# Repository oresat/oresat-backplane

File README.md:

# OreSat Backplane

## Background

The [OreSat](http://oresat.org) CubeSat bus uses a card cage / backplane system based on a 1 Mbps Controller Area Network (CAN) bus and a 2 cell Lithium ion battery power bus (6.0 - 8.4 V). There are ~ 8 cards per CubeSat "U", and the board is meant to be general purpose enough to allow for some card swapping. The RF lines, however, are microstrips on the backplane PCB so the backplane must be rev'd for changes in the RF cards. There are three sets of connectors:

1. 40 pin "Main" connector, which has !shutdown, CAN1, power, CAN2, OreSat power Domain (OPD) lines, and then 5 shared spare pins for custom card interconnects.
2. SMPM RF conncectors, which allows up to 3 RF connector per card and allows for 50 ohm microstrips to be run up and down the the board.
3. 20 pin "Auxiliary" connectors, used on the all but the "end" cards (top and bottom cards), which are for future inter-card communication. Good for Ethernet, for example.

The backplane now comes in two flavors: a 1U backplane, and a 2U backplane.

## Mechanical Specifications

All mechanical specifications for this board are from the SolidWorks model which is in the 'oresat-structure' repo, specifically see the 'Backplane' folder. Some notes on the mechanical design:

- Ring of bare copper on the back is for thermal contact. Assumes annodized Aluminum, so no electrical contact on this ring.
- Backplane is grounded to the Aluminum frame on the internal four fasteners; this requires preparing the Aluminum for an electrical connection.
- Square cutouts on the top and bottom are for the solar connectors to reach the end cards. Note that on the 1U backplane, the bottom cutout is not used.
- Weird cutouts above and below square solar connector cutouts are for shoulder bolts (3 mm Shoulder Diameter, 2 mm Shoulder Length, M2 x 0.4 mm Thread, McMaster Carr #[90263A111](https://www.mcmaster.com/90263a111)) that precisely locates the PCB while allowing some flexing due to differences in thermal expansion between the Aluminum frame and the PCB.
- All other fasteners are M2 x 0.4 x 4 mm.

## Electrical Specifications

The board is designed for a [4 layer stackup](https://docs.oshpark.com/services/four-layer/) from [OSH Park](https://oshpark.com/) which has better RF performance than regular 2 layer board runs.

The connectors that we use on this puppy are the:

- **1.27 mm through-hole vertical socket connectors:**
    - 40 pin main connector
       - Samtec SFM-120-01-S-D-LC
       - 3D CAD: https://www.samtec.com/partnumber/sfm-120-01-s-d-lc
       - Drawing: http://suddendocs.samtec.com/prints/sfm-1xx-xx-xxx-d-xxx-mkt.pdf
       - Brochure: http://suddendocs.samtec.com/catalog_english/sfm.pdf
       - SFM footprint: http://suddendocs.samtec.com/prints/sfm-thd.pdf
    - 20 pin auxiliary connector
       - Samtec SFM-110-01-S-D-LC
       - 3D CAD: https://www.samtec.com/partnumber/sfm-110-01-s-d-lc
       - Drawing: http://suddendocs.samtec.com/prints/sfm-1xx-xx-xxx-d-xxx-mkt.pdf
       - Brochure: http://suddendocs.samtec.com/catalog_english/sfm.pdf
       - SFM footprint: http://suddendocs.samtec.com/prints/sfm-thd.pdf

- **RF (70 cm, L band, S band)**
   - Molex 073300-011X
   - SMPM Connector Plug, Male Pin 50 Ohm Surface Mount, Through Hole Solder, $13.84/ea @ 10
   - Molex (w/CAD): https://www.molex.com/molex/products/datasheet.jsp?part=active/0733000110_RF_COAX_CONNECTORS.xml&channel=Products&Lang=en-US
   - We've done a detailed characteraziation of OSH Park's 4 layer process, and found that 0.38 mm is the correct width for a 50 ohm microstrip.

- **CAN termination**
   - We'll use split termination, using two 60 ohm resistors with a center tapped capacitor for reduced EMI.
   - Resistors
      - 60.4 +/- 1% ohms. Might consider higher if the number of notes (~ 20) adds too much parallel resistance)
      - Usually there's only 2V (differential) across the 120 ohm termination resistors = 16 mA = 33 mW of power dissipation.
      - In the event of a bus short, there's 8.4 V across 120 ohms is 70 mA = 590 mW of power dissipation. That's ~ 300 mW across each of the 60 ohm resistors. Yikes.
      - ISO 11898-2 also requires 220 mW for the termination resistors, for whatever that's worth.
      - There exist 0.5 W 1206 resistors (?!) so although that's for an air rating, we'll still choose it, since larger than 1206 resistors are a tight fit
   - Capacitor
      - ISO 11898-2 doesn't seem to say anything about the capacitance, and the internets tend to say weird things. Unclear on this value.
      - TI's [Controller Area Network Physical Layer Requirements](http://www.ti.com/lit/an/slla270/slla270.pdf) suggests 4.7 nF to make the f_3dB = 1.1 MHz.
      - Seems awfully close to our 1 Mbps bus, so let's bump that down to 1 nF which is f_3db = 5.3 MHz.

- **Debug connector**
   - Harwin M55-6001642R (same family as the solar and end cap connectors)
   - Located on the back side of the backplane, it's a 16 pin 1.27 mm connector that gives external access to CAN busses, VBUS, and the UART lines. It sits in the 1U solar module "cutout".
   - For the external connector board, see the `backplane-debug` folder in the `oresat-flatsat` repo.

## Versions

- 1U
   - v1.0 - First fabbed 1U, but never assembled. For old frames (v1.1 frames), no -Z end cap connector, no debug connector.
   - v1.1 - Added -Z end cap connector. Fabbed roughly 2020-09-01, two assembled.
   - v1.2 - Added 1.27 mm debug connector, which tended to short. Fabbed 2020-12-08. Originally delivered on OreSat0.0 but never flown.
   - v2.0 -new backplane "v2" signal pinout (less power, more signals, UART lines, CAN bus bridging) and new non-shorting debug connector. Made new debug port board and breakout. Also corrected RF ports, including L1 band microstrip and S band strip to -Z end cap. Fabbed 2021-11-01 and installed on OreSat0.1 handed off to Spaceflight, ready for launch!
- 2U
   - v1.0 - First backplane. 2 layer board, RF connector array, aux and main connectors. Fabbed 2018/10/02.
   - v1.1 - End Cards now use 40 pin connector, solar connectors now actually fit. Fabbed 2019/02/25.
   - V2.0 - Switched to 4 layer board, removed RF connector array, used actual microstrips tuned to the 4 layer OSH Park process. Fabbed 2019/07/01.
   - v2.1 - Updated to latest backplane DXF, reducing all sides by 0.15 mm. Fixed solar connector cutout areas that were lopsided. Added CAN termination resistors. Moved RF connectors to latest (2020/02/15) locations. NOT YET FABBED.
   - vHASP - Made for the NASA HASP mission, fabbed, but never used.
   - V2.2 - Updated to FrameV2 and Oresat0.5 card locations

## LICENSE

Copyright the Portland State Aerospace Society, 2022.

This source describes Open Hardware that is licensed under CERN-OHL-S v2, or any later version.

You may redistribute and modify this source and make products using it under the terms of the CERN-OHL-S v2 (https://ohwr.org/cern_ohl_s_v2.txt).

This source is distributed WITHOUT ANY EXPRESS OR IMPLIED WARRANTY, INCLUDING OF MERCHANTABILITY, SATISFACTORY QUALITY AND FITNESS FOR A PARTICULAR PURPOSE. Please see the CERN-OHL-S v2 for applicable conditions.

Source location: https://github.com/oresat/

As per CERN-OHL-S v2 section 4, should You produce hardware based on this source, You must where practicable maintain the Source Location visible on the external case of the Gizmo or other products you make using this source.

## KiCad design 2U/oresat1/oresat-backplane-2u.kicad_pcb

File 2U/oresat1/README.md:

---
title: "**OreSat1 2U Backplane Fabrication and Assembly Information**"
subtitle: |
  **Fabrication and Assembly Information**\
  For build TIME-STAMP
fontsize: 10pt
geometry:
  - margin=0.5in
toc: true
toc-depth: 2
colorlinks: true
urlcolor: blue
---

\newpage

# About this Board

## Board Description

The OreSat1 2U Backplane is the backplane for a 2U CubeSat based on the open source [OreSat CubeSat system](https://www.oresat.org/). The backplane has:

- 40 pin main connnectors for Oresat-based cards
- Bus voltage (2S Lithium Ion batteries with a Vnom of 7.2V)
- Two CAN busses for inter-card communication
- RF lines using SMPM RF connectors and microstrips
- A debug connector to carry critical lines to the outside of the CubeSat
- Two cutouts for solar module connections

## Documentation Links

- OreSat Backplane hardware Git repository: <https://github.com/oresat/oresat-backplane>
- **TODO:** Backplane Design Notes + Design Review Notes

## Documentation Files

| Filename                        | Notes                                    |
| ------------------------------- | ---------------------------------------- |
| README.pdf                      | This README file                         |
| PROJECT-NAME-outline.dxf        | Board outline (with holes) in DXF format |
| PROJECT-NAME-pcba.step          | 3D model of PCBA (with components)       |
| PROJECT-NAME-render-bot.jpg     | Render of the top of the 3D model        |
| PROJECT-NAME-render-bot.jpg     | Render of the bottom of the 3D model     |
| PROJECT-NAME-schematic.pdf      | PDF of board schematics                  |

## Contact Information

- Website: <https://www.oresat.org/>
- Email: <oresat@pdx.edu>
- Instagram: @pdxaerospace

## Board Renders

{width=50%}
{width=50%}

\newpage

# Printed Circuit Board (PCB) Fabrication Information

## Board Info

- 4 layer board
- Bounding box is 82.5 x 213.5 mm
- Board thickness is 1.59 mm (0.063 inch)
- **Important:** See Materials and Stack Up sections below

## Board Requirements

- Design Rules
    - Minimum Trace / Space design rules
       - Outer layers: 0.127 mm (5.0 mil) / 0.127 mm (5.0 mil)
       - Inner layers: 0.127 mm (5.0 mil) / 0.127 mm (5.0 mil)
    - Outer dimension router tolerance: +/- 0.254 mm (10.0 mil)
    - Hole placement tolerance: +/- 0.075 mm (3.0 mil)
    - Inner tab routed slot tolerance: +/- 0.254 mm (10.0 mil)
- Drills
   - Drill Positional Tolerance: 0.051 mm (2.0 mil)
   - Drill Size tolerance: +/- 0.064 mm (2.5 mil)
- Plated/Un-plated holes
  - PTH minimum diameter: 0.254 mm (10 mil)
  - PTH minimum annulus: 0.102 mm (4 mil) radius
  - There are 4 un-plated (NPT) holes
- Outline/Routing
  - Requires a 1.0 mm or smaller diameter routing bit
- Slots/Cutouts
  - There are two slot/cutouts.
  - Requires a 1.0 mm or smaller diameter routing bit
- There are 3 fiducials on the top layer and 3 fiducials on the bottom layer.
- Panel tabs ("mouse bites")
   - Card edges must be smooth; no mouse bites or other intrusions into the card outline.
   - If external mouse bites are required, minimize and customer will remove by hand before assembly.
- If not otherwise specified, PCB fabrication shall conform to IPC-6012, Class 2 or better. 
- If not otherwise specified, PCB acceptability criteria shall be via IPC-A-600, Class 2 or better.

## Materials

- Controlled impedance
   - The stackup is critical for the performance of high speed signals on this board.
   - As long as the stackup is controlled, the board is not considered controlled impedance.
- Isola FR408HR or material with equivalent Dk.
- Board Surface treatment should be ENIG, althogh immersion Silver is acceptable.
- White silkscreen on top and bottom surface
- Taiyo PSR-4000 or equivalent soldermask on top and bottom, no requirements for color.

## Stack Up

| Layer         | Thickness           | Notes                                        |
|---------------|---------------------|----------------------------------------------|
| Top Copper    | 0.043 mm /  1.7 mil |  Layer 1 foil, 1 oz Cu after plating         |
| prepreg       | 0.200 mm /  7.9 mil |  Prepreg - Isola FR408HR 2113                |
| Layer 2       | 0.018 mm /  0.7 mil |  Layer 2 foil, 0.5 oz Cu                     |
| Core          | 0.991 mm /   39 mil |  Core Isola FR408HR                          |
| Layer 3       | 0.018 mm /  0.7 mil |  Layer 3 foil, 0.5 oz Cu                     |
| prepreg       | 0.200 mm /  7.9 mil |  Prepreg - Isola FR408HR 2113                |
| Bottom Copper | 0.043 mm /  1.7 mil |  Layer 4 foil, 1 oz copper after plating     |
| **Total Stackup** | **1.588 mm / 62.5 mil** |                                      |

## Array / Panel Information

- Coordinate with Contract Manufacturer (CM) for optimal size of this panel.
- If no feedback from CM, then produce single boards (no panel).

## Fabrication Files

### IPC-2581 File

| Filename                 | Notes                                   |
| ------------------------ | --------------------------------------- |
| PROJECT-NAME-ipc2581.xml | IPC-2581 board information file         |

### Legacy PCB Files

| Filename                      | Notes                                         |
| ------------------------------| --------------------------------------------- |
| PROJECT-NAME-Edge_Cuts.gbr    | RS274X file for the dimension (outline) layer |
| PROJECT-NAME-F_Silkscreen.gbr | RS274X file for the top silkscreen            |
| PROJECT-NAME-F_Mask.gbr       | RS274X file for the top soldermask            |
| PROJECT-NAME-F_Cu.gbr         | RS274X file for the top copper layer          |
| PROJECT-NAME-In1_Cu.gbr       | RS274X file for the layer 2 copper            |
| PROJECT-NAME-In2_Cu.gbr       | RS274X file for the layer 3 copper            |
| PROJECT-NAME-B_Cu.gbr         | RS274X file for the bottom copper layer       |
| PROJECT-NAME-B_Mask.gbr       | RS274X file for the bottom soldermask         |
| PROJECT-NAME-B_Silkscreen.gbr | RS274X file for the bottom silkscreen         |
| PROJECT-NAME-NPTH.drl         | Excellon file for non-plated through holes    |
| PROJECT-NAME-PTH.drl          | Excellon file for plated through holes        | 

\newpage

# Printed Circuit Board Assembly (PCBA) Information

## Assembly Info

- There are components on the top and bottom sides of the board.
- This PCBA is a mix of surface mount (SMT) and through hole (THT) components.

## Assembly Requirements

- Assembly shall conform to IPC J-STD-001 Class 2 or better.
- Inspection of assemblies shall be per IPC-A-610, Class 2 or better.
- Bake components that are not moisture sealed to appropriate levels as required.
- Solder paste MUST be leaded.
- Aqueous flux and wash strongly preferred.
   - Clean to NASA Standard "Visibly Clean (VC)": No particles or residues are visible to the naked eye.
- No conformal coating.
- Ship in antistatic protective bag.

## Component Specific Assembly Information

- SMPM connectors (CM*.*) should be hand-added before reflow.

## Assembly Files

### IPC-2581 File

| Filename                 | Notes                           |
| ------------------------ | ------------------------------- |
| PROJECT-NAME-ipc2581.xml | IPC-2581 board information file |

### Bill of Materials (BOM)

| Filename             | Description                            |
| -------------------- | -------------------------------------- |
| PROJECT-NAME-bom.csv | BOM in Comma Separated Variable format |

### Solder Paste Stencils

| Filename                 | Notes                                            |
| ------------------------ | ------------------------------------------------ |
| PROJECT-NAME-B_Paste.gbr | RS274X file for top/front solder paste stencil   |
| PROJECT-NAME-F_Paste.gbr | RS274X file for bottom/back solder paste stencil |

### Mounting/Placement Location

| Filename            | Description                                 |
| ------------------- | ------------------------------------------- |
| PROJECT-NAME-3u.pos | Pick and place locations for components     |

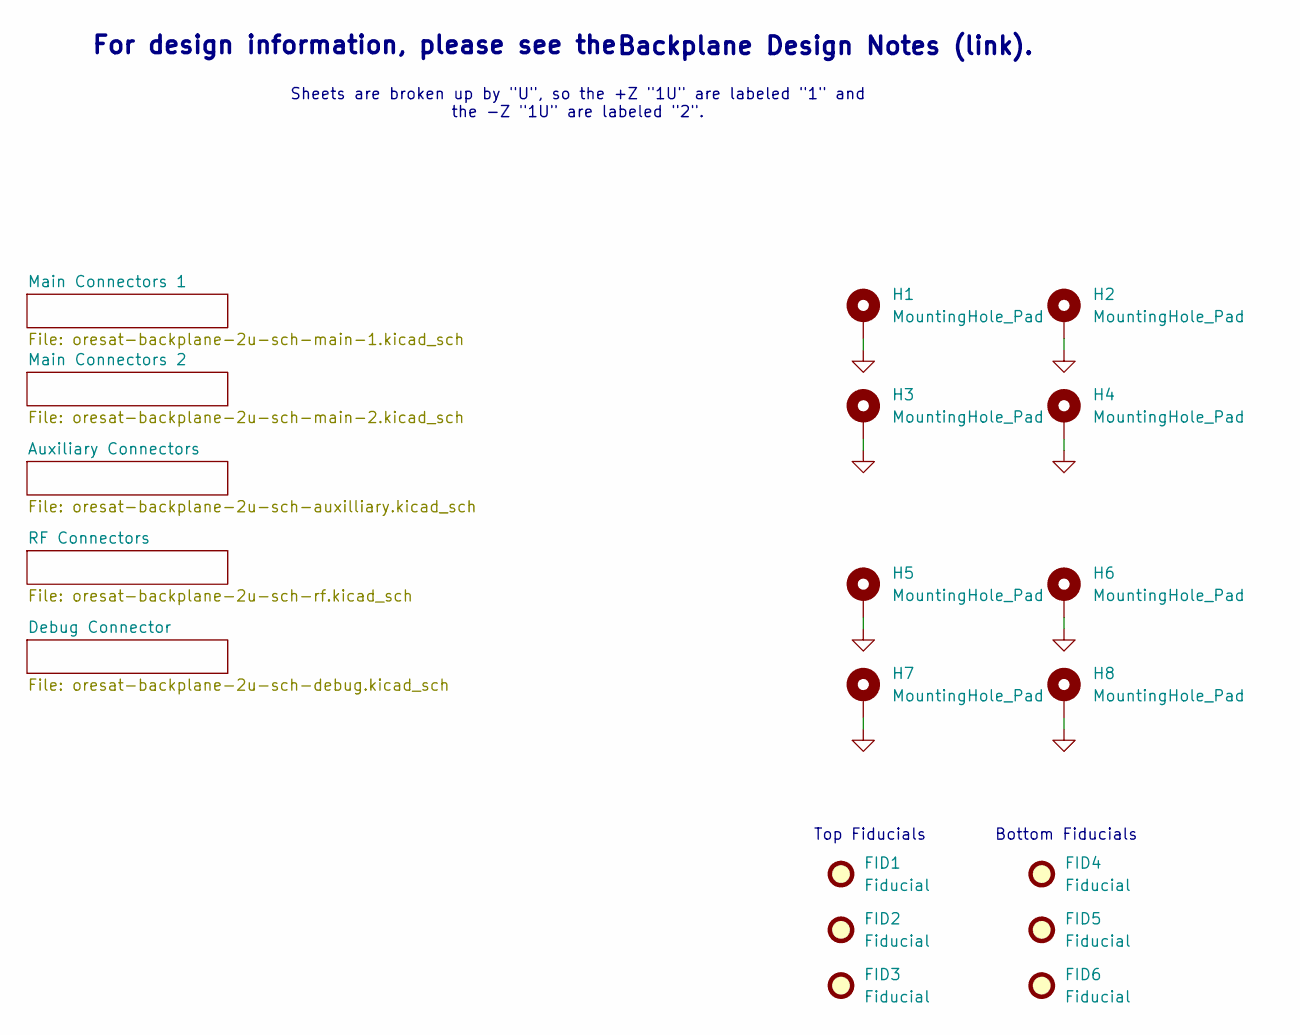
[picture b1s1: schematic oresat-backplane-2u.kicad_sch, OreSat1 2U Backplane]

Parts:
FID1, FID2, FID3, FID4, FID5, FID6: Fiducial; Fiducial_1mm_Mask2mm
H1, H2, H3, H4, H5, H6, H7, H8: MountingHole_Pad; MountingHole_2.2mm_M2_DIN965_Pad

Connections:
GND: H1.1 (1_1), H2.1 (1_1), H3.1 (1_1), H4.1 (1_1), H5.1 (1_1), H6.1 (1_1), H7.1 (1_1), H8.1 (1_1); also elsewhere on the board

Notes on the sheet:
For design information, please see the
Top Fiducials
Sheets are broken up by "U", so the +Z "1U" are labeled "1" and the -Z "1U" are labeled "2".
Backplane Design Notes (link).
Bottom Fiducials

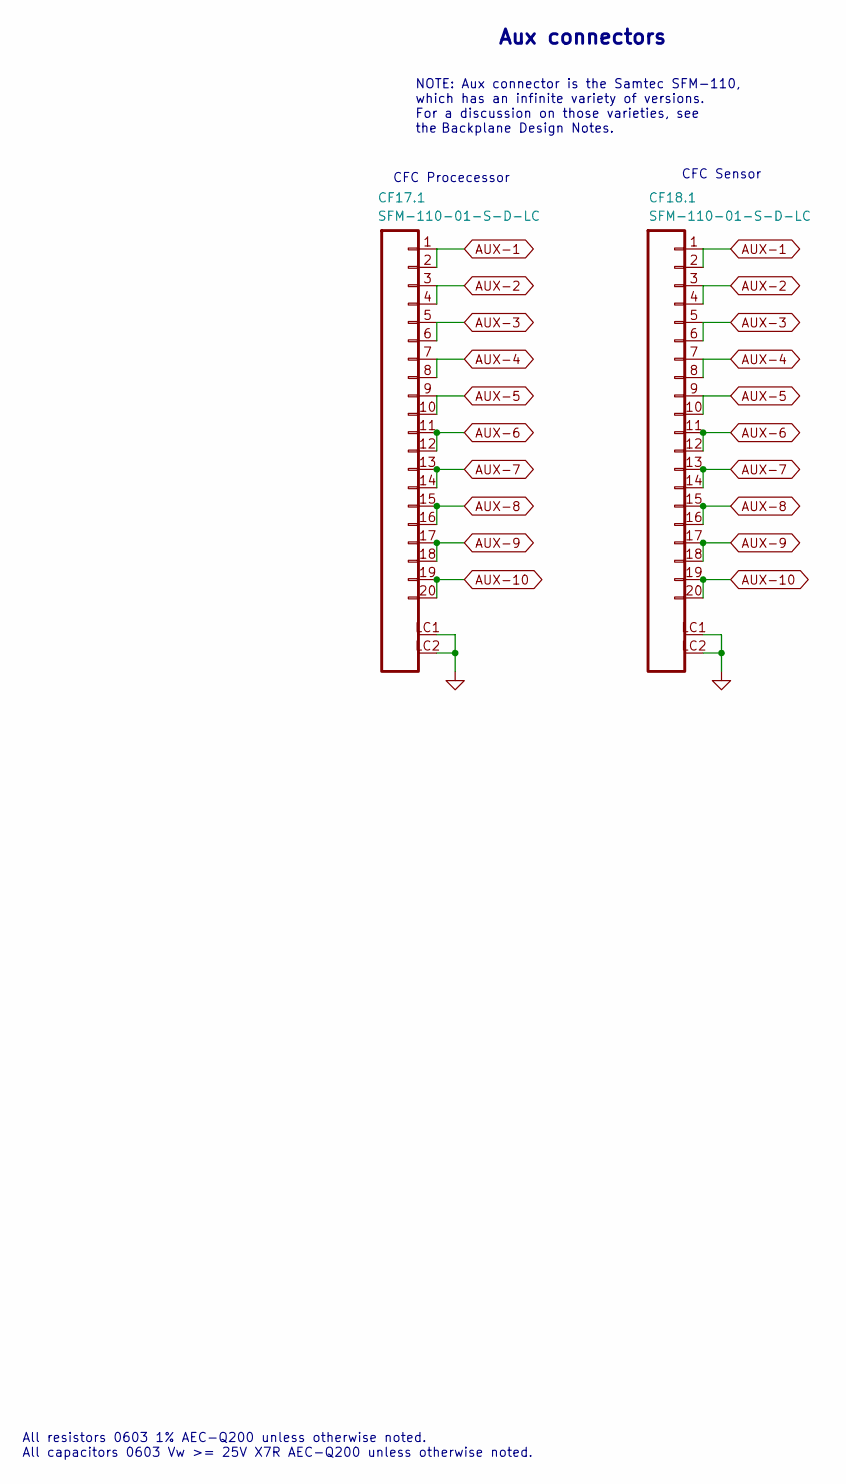
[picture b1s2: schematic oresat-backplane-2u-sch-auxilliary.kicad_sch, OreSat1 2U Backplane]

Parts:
CF17.1, CF18.1: SFM-110-01-S-D-LC; J-SAMTEC-CF-SFM-110-X1-XXX-D-LC; MPN SFM-110-01-S-D-LC

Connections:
AUX-1: CF17.1.1, CF17.1.2, CF18.1.1, CF18.1.2
AUX-2: CF17.1.3, CF17.1.4, CF18.1.3, CF18.1.4
AUX-3: CF17.1.5, CF17.1.6, CF18.1.5, CF18.1.6
AUX-4: CF17.1.7, CF17.1.8, CF18.1.7, CF18.1.8
AUX-5: CF17.1.9, CF17.1.10, CF18.1.9, CF18.1.10
AUX-6: CF17.1.11, CF17.1.12, CF18.1.11, CF18.1.12
AUX-7: CF17.1.13, CF17.1.14, CF18.1.13, CF18.1.14
AUX-8: CF17.1.15, CF17.1.16, CF18.1.15, CF18.1.16
AUX-9: CF17.1.17, CF17.1.18, CF18.1.17, CF18.1.18
AUX-10: CF17.1.19, CF17.1.20, CF18.1.19, CF18.1.20
GND: CF17.1.LC1, CF17.1.LC2, CF18.1.LC1, CF18.1.LC2; also elsewhere on the board

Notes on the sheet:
Backplane Design Notes.
CFC Procecessor
All resistors 0603 1% AEC-Q200 unless otherwise noted. All capacitors 0603 Vw >= 25V X7R AEC-Q200 unless otherwise noted.
CFC Sensor
NOTE: Aux connector is the Samtec SFM-110, which has an infinite variety of versions. For a discussion on those varieties, see the
Aux connectors

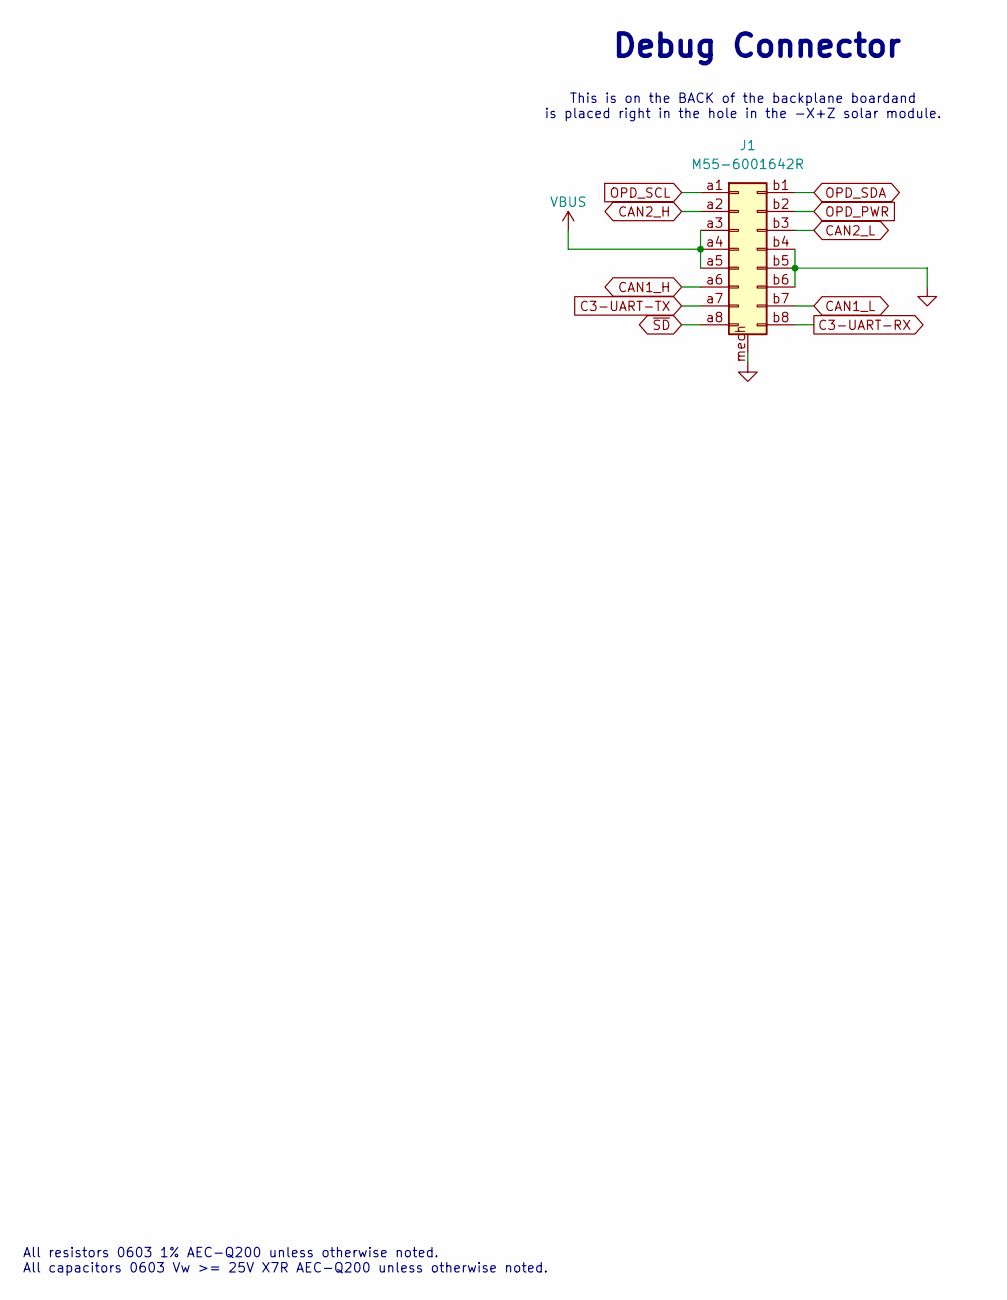
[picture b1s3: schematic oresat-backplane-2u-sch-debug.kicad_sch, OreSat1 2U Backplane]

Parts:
J1: M55-6001642R; m55-6001642; MPN M55-6001642R

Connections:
C3-UART-RX: J1.b8; also elsewhere on the board
C3-UART-TX: J1.a7; also elsewhere on the board
CAN1_H: J1.a6; also elsewhere on the board
CAN1_L: J1.b7; also elsewhere on the board
CAN2_H: J1.a2; also elsewhere on the board
CAN2_L: J1.b3; also elsewhere on the board
GND: J1.b4, J1.b5, J1.b6, J1.mech; also elsewhere on the board
OPD_PWR: J1.b2; also elsewhere on the board
OPD_SCL: J1.a1; also elsewhere on the board
OPD_SDA: J1.b1; also elsewhere on the board
VBUS: J1.a3, J1.a4, J1.a5; also elsewhere on the board
~SD: J1.a8; also elsewhere on the board

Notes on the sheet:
This is on the BACK of the backplane boardand is placed right in the hole in the -X+Z solar module.
Debug Connector
All resistors 0603 1% AEC-Q200 unless otherwise noted. All capacitors 0603 Vw >= 25V X7R AEC-Q200 unless otherwise noted.

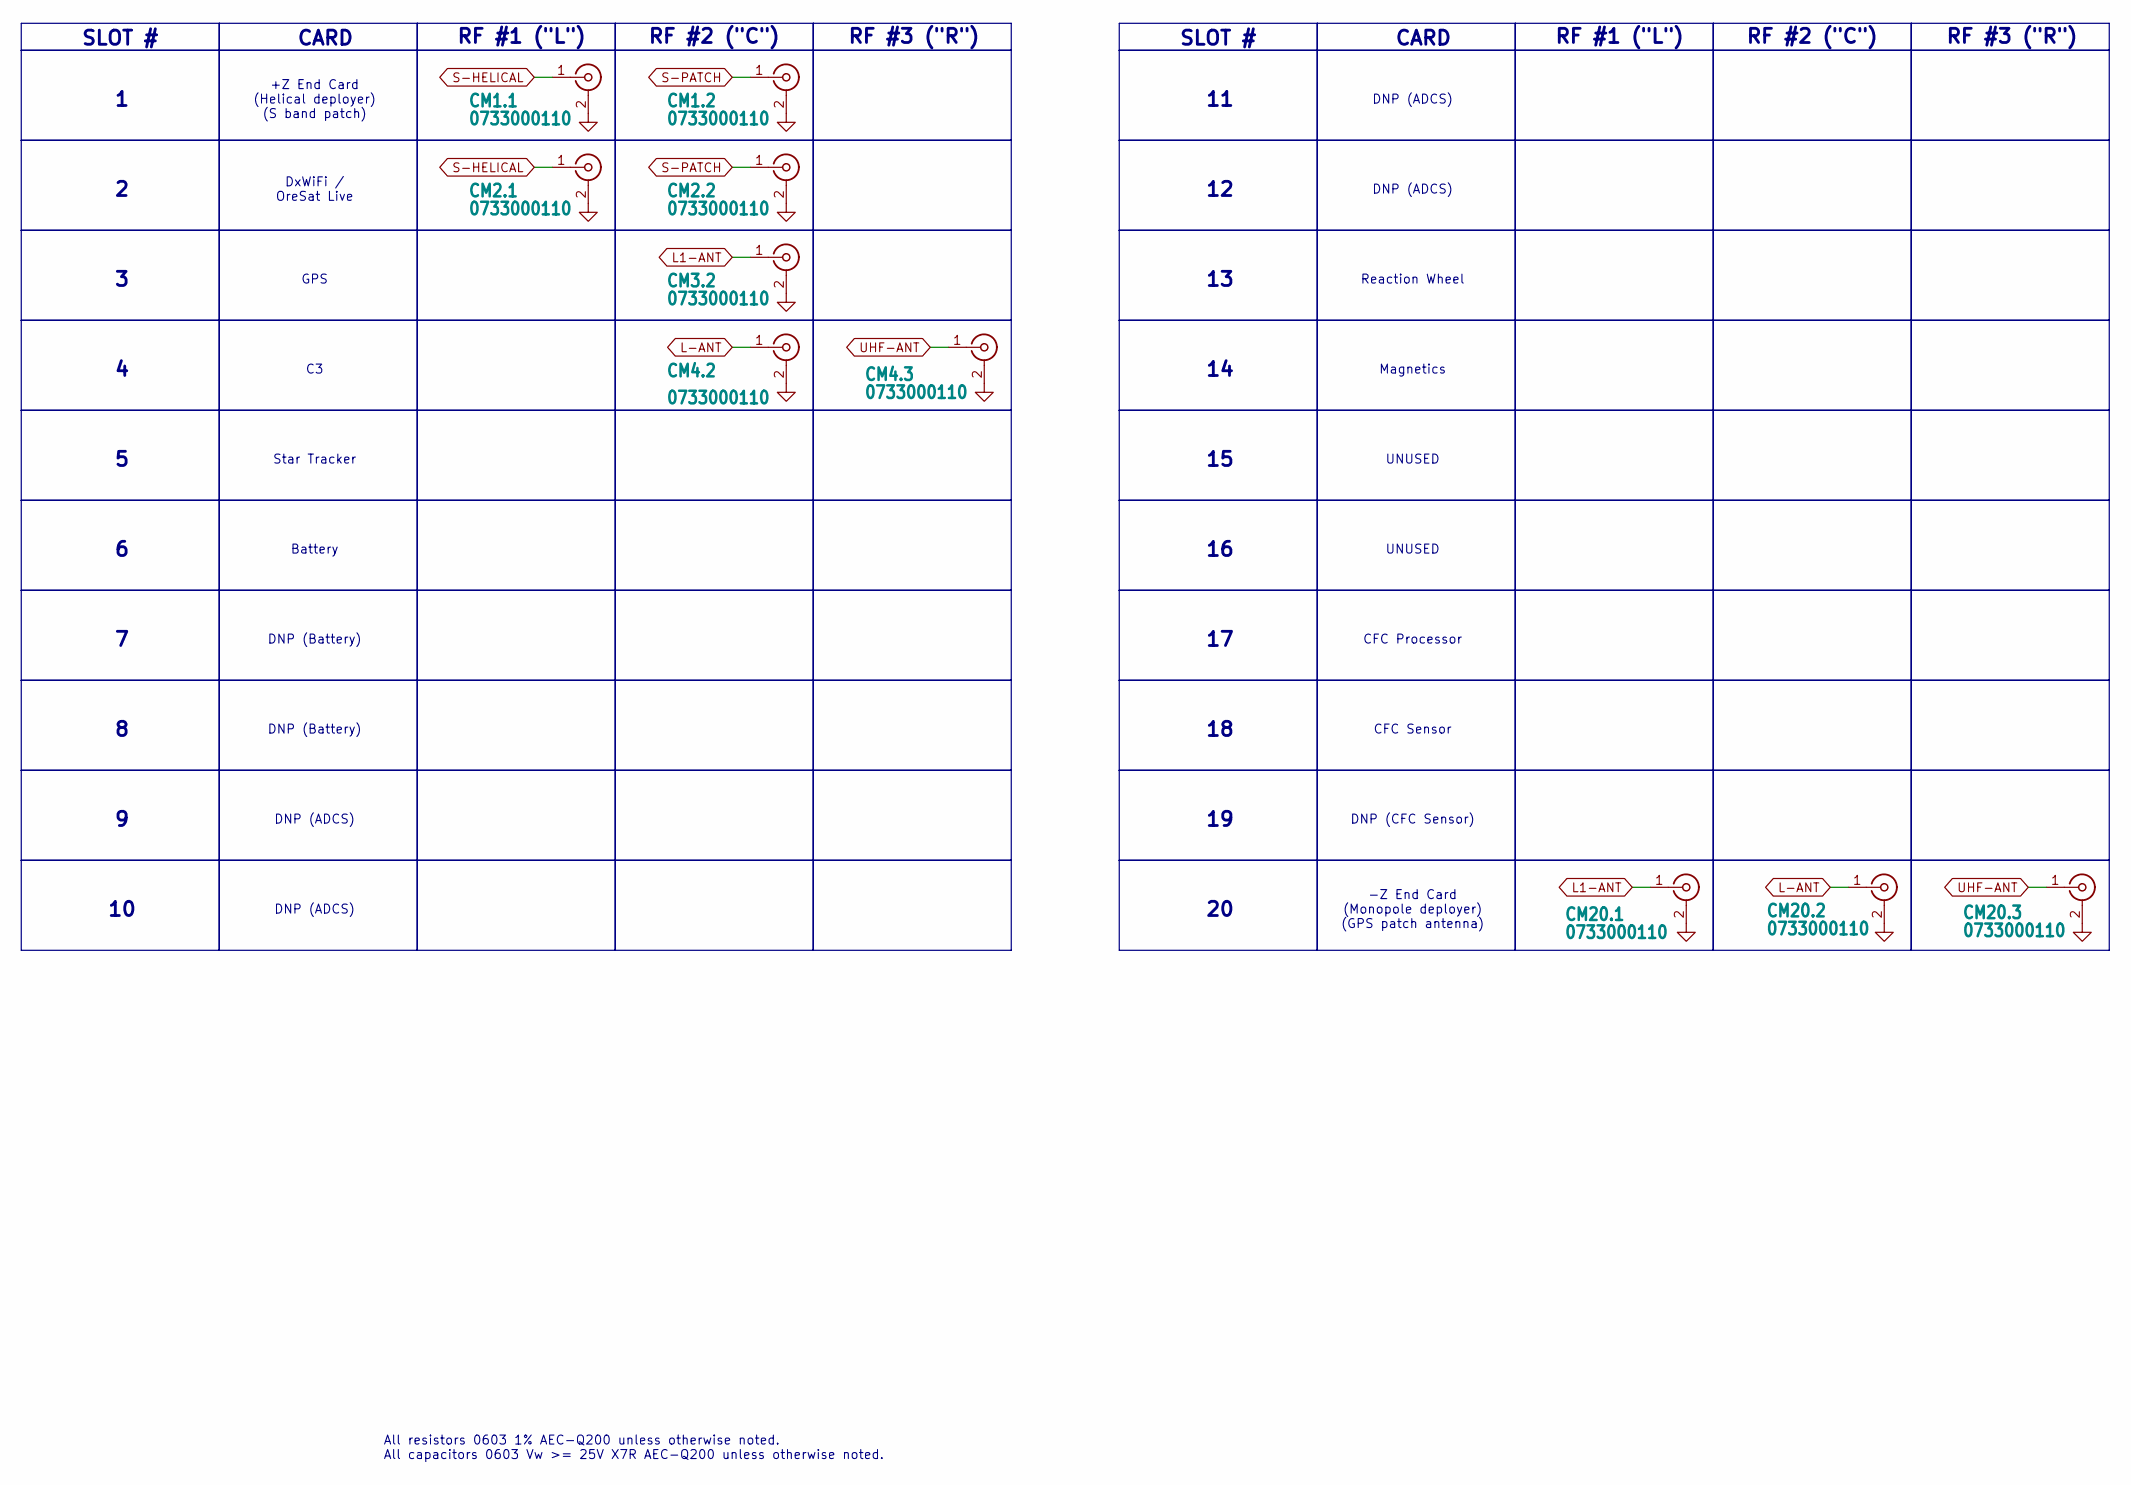
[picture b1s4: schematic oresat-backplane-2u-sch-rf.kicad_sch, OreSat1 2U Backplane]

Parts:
CM1.1, CM1.2, CM2.1, CM2.2, CM3.2, CM4.2, CM4.3, CM20.1, CM20.2, CM20.3: 0733000110; J-MOLEX-SMPM-73300-011X; MPN 0733000110

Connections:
GND: CM1.1.2 (Ext), CM1.2.2 (Ext), CM2.1.2 (Ext), CM2.2.2 (Ext), CM3.2.2 (Ext), CM4.2.2 (Ext), CM4.3.2 (Ext), CM20.1.2 (Ext), CM20.2.2 (Ext), CM20.3.2 (Ext); also elsewhere on the board
L1-ANT: CM3.2.1 (In), CM20.1.1 (In)
L-ANT: CM4.2.1 (In), CM20.2.1 (In)
S-HELICAL: CM1.1.1 (In), CM2.1.1 (In)
S-PATCH: CM1.2.1 (In), CM2.2.1 (In)
UHF-ANT: CM4.3.1 (In), CM20.3.1 (In)

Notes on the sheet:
CARD
SLOT #
+Z End Card (Helical deployer) (S band patch)
RF #2 ("C")
RF #3 ("R")
DxWiFi / OreSat Live
UNUSED
Star Tracker
Battery
DNP (CFC Sensor)
GPS
RF #1 ("L")
DNP (ADCS)
CFC Sensor
Magnetics
CFC Processor
-Z End Card (Monopole deployer) (GPS patch antenna)
DNP (Battery)
Reaction Wheel
All resistors 0603 1% AEC-Q200 unless otherwise noted. All capacitors 0603 Vw >= 25V X7R AEC-Q200 unless otherwise noted.

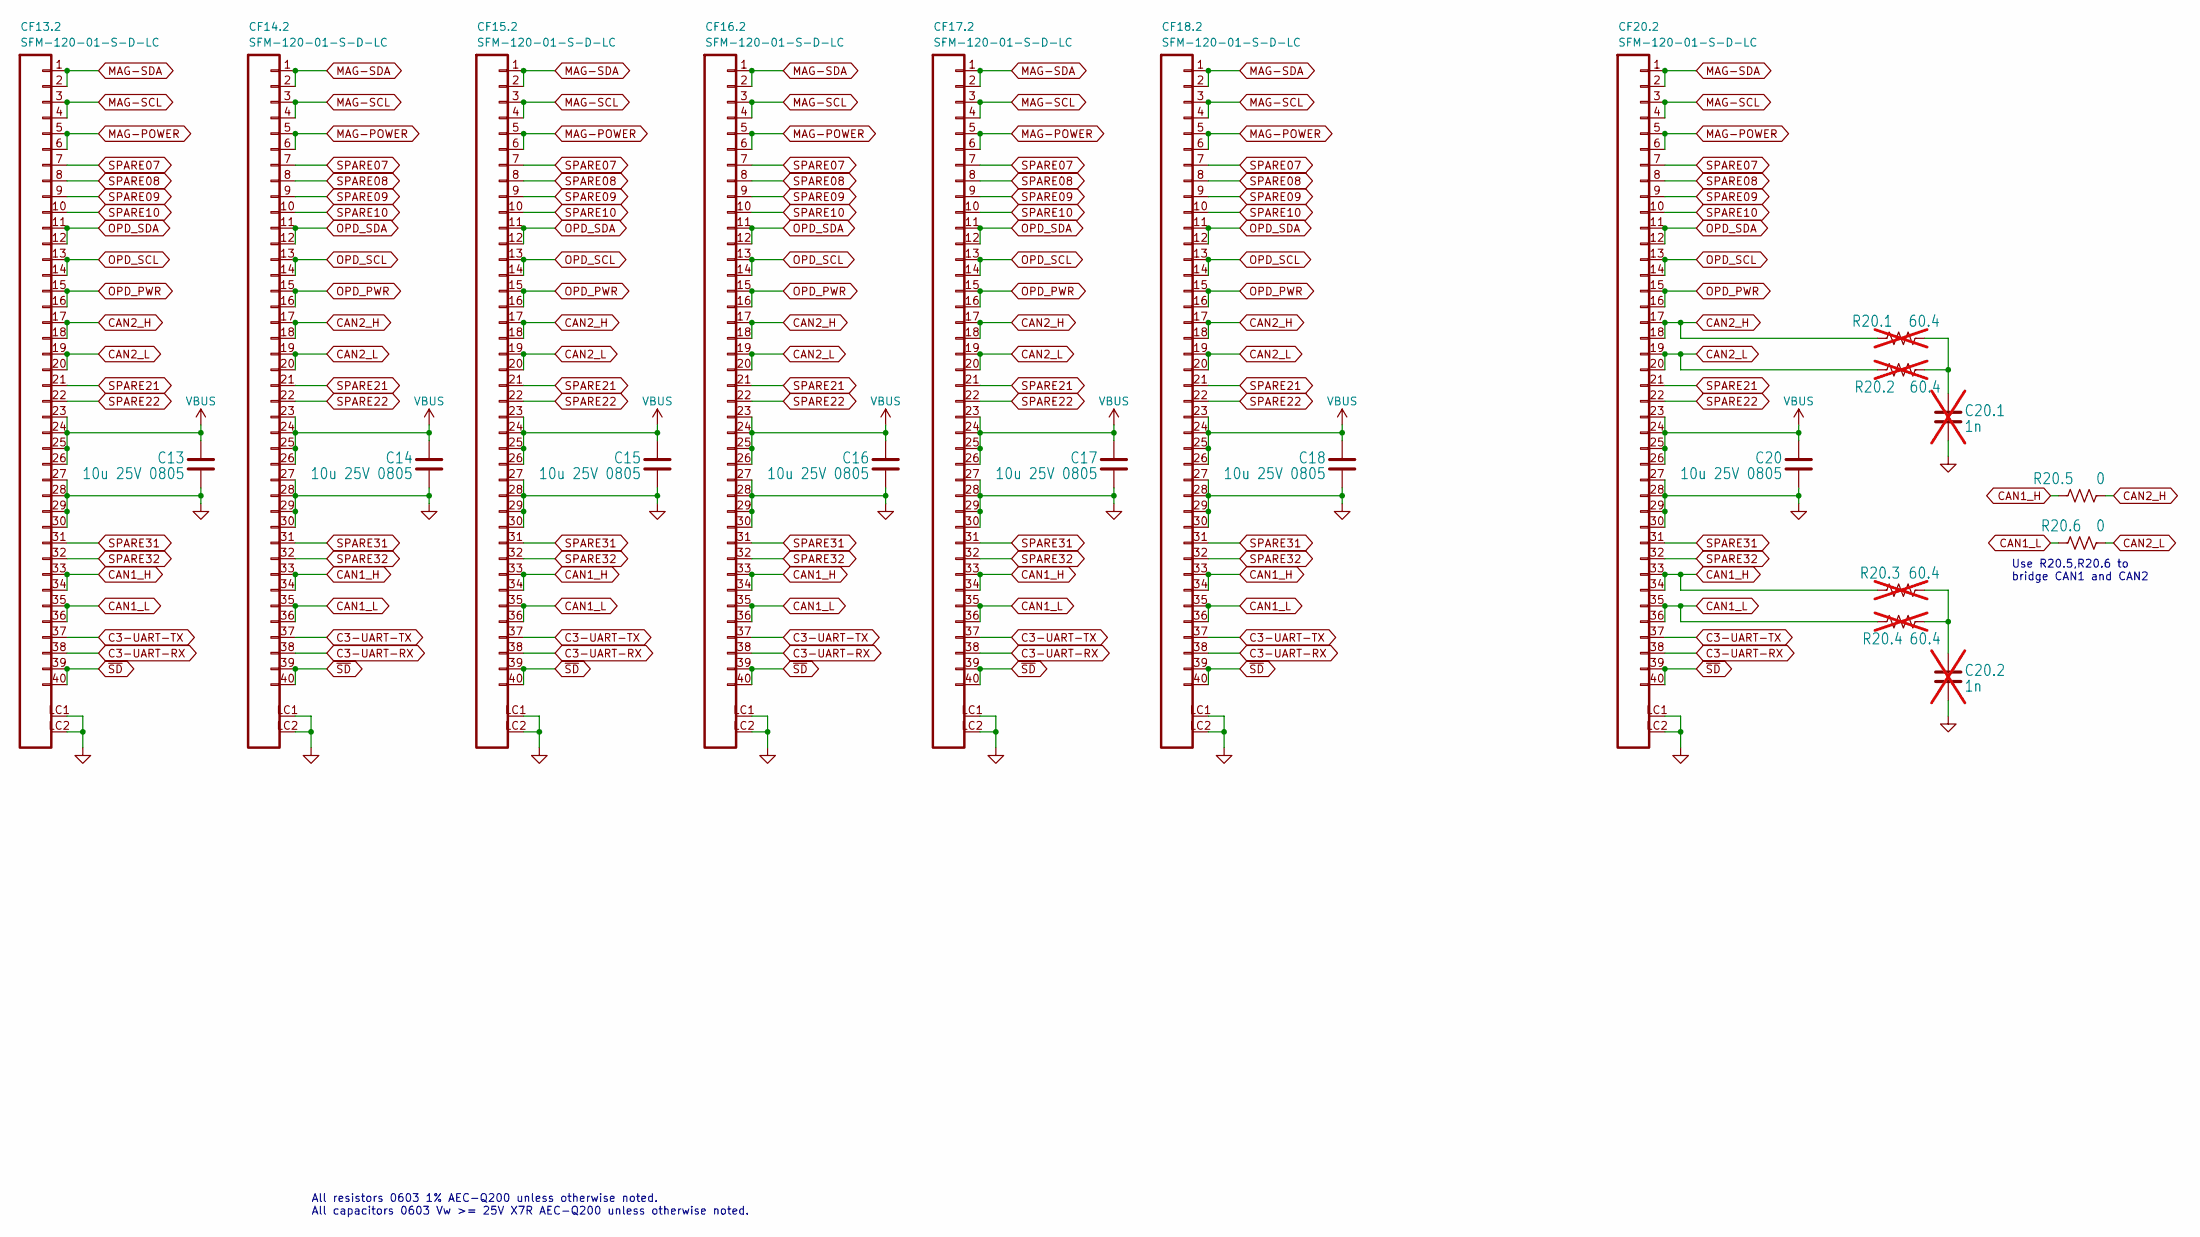
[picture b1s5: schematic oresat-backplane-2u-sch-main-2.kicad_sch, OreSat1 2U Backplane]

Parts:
C13, C14, C15, C16, C17, C18, C20: 10u 25V 0805; C_1206_3216Metric; MPN GRT31CR71E106KE13L
C20.1, C20.2: 1n; 0603-C-NOSILK; MPN C0603C102J5GECAUTO; not fitted
CF13.2, CF14.2, CF15.2, CF16.2, CF17.2, CF18.2, CF20.2: SFM-120-01-S-D-LC; J-SAMTEC-SFM-120-X1-XXX-D; MPN SFM-120-01-S-D-LC
R20.1, R20.2, R20.3, R20.4: 60.4; R_1206_3216Metric; MPN RMCF1206FT60R4; not fitted
R20.5, R20.6: 0; 0603-C-NOSILK; MPN RMCF0603ZT0R00

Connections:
C3-UART-RX: CF13.2.38, CF14.2.38, CF15.2.38, CF16.2.38, CF17.2.38, CF18.2.38, CF20.2.38; also elsewhere on the board
C3-UART-TX: CF13.2.37, CF14.2.37, CF15.2.37, CF16.2.37, CF17.2.37, CF18.2.37, CF20.2.37; also elsewhere on the board
CAN1_H: CF13.2.33, CF13.2.34, CF14.2.33, CF14.2.34, CF15.2.33, CF15.2.34, CF16.2.33, CF16.2.34, CF17.2.33, CF17.2.34, CF18.2.33, CF18.2.34, CF20.2.33, CF20.2.34, R20.3.1, R20.5.1; also elsewhere on the board
CAN1_L: CF13.2.35, CF13.2.36, CF14.2.35, CF14.2.36, CF15.2.35, CF15.2.36, CF16.2.35, CF16.2.36, CF17.2.35, CF17.2.36, CF18.2.35, CF18.2.36, CF20.2.35, CF20.2.36, R20.4.2, R20.6.1; also elsewhere on the board
CAN2_H: CF13.2.17, CF13.2.18, CF14.2.17, CF14.2.18, CF15.2.17, CF15.2.18, CF16.2.17, CF16.2.18, CF17.2.17, CF17.2.18, CF18.2.17, CF18.2.18, CF20.2.17, CF20.2.18, R20.1.1, R20.5.2; also elsewhere on the board
CAN2_L: CF13.2.19, CF13.2.20, CF14.2.19, CF14.2.20, CF15.2.19, CF15.2.20, CF16.2.19, CF16.2.20, CF17.2.19, CF17.2.20, CF18.2.19, CF18.2.20, CF20.2.19, CF20.2.20, R20.2.2, R20.6.2; also elsewhere on the board
GND: C13.2, C14.2, C15.2, C16.2, C17.2, C18.2, C20.2, C20.1.2, C20.2.2, CF13.2.27, CF13.2.28, CF13.2.29, CF13.2.30, CF13.2.LC1, CF13.2.LC2, CF14.2.27, CF14.2.28, CF14.2.29, CF14.2.30, CF14.2.LC1, CF14.2.LC2, CF15.2.27, CF15.2.28, CF15.2.29, CF15.2.30, CF15.2.LC1, CF15.2.LC2, CF16.2.27, CF16.2.28, CF16.2.29, CF16.2.30, CF16.2.LC1, CF16.2.LC2, CF17.2.27, CF17.2.28, CF17.2.29, CF17.2.30, CF17.2.LC1, CF17.2.LC2, CF18.2.27, CF18.2.28, CF18.2.29, CF18.2.30, CF18.2.LC1, CF18.2.LC2, CF20.2.27, CF20.2.28, CF20.2.29, CF20.2.30, CF20.2.LC1, CF20.2.LC2; also elsewhere on the board
MAG-POWER: CF13.2.5, CF13.2.6, CF14.2.5, CF14.2.6, CF15.2.5, CF15.2.6, CF16.2.5, CF16.2.6, CF17.2.5, CF17.2.6, CF18.2.5, CF18.2.6, CF20.2.5, CF20.2.6; also elsewhere on the board
MAG-SCL: CF13.2.3, CF13.2.4, CF14.2.3, CF14.2.4, CF15.2.3, CF15.2.4, CF16.2.3, CF16.2.4, CF17.2.3, CF17.2.4, CF18.2.3, CF18.2.4, CF20.2.3, CF20.2.4; also elsewhere on the board
MAG-SDA: CF13.2.1, CF13.2.2, CF14.2.1, CF14.2.2, CF15.2.1, CF15.2.2, CF16.2.1, CF16.2.2, CF17.2.1, CF17.2.2, CF18.2.1, CF18.2.2, CF20.2.1, CF20.2.2; also elsewhere on the board
unnamed: C20.1.1, R20.1.2, R20.2.1
unnamed: C20.2.1, R20.3.2, R20.4.1
OPD_PWR: CF13.2.15, CF13.2.16, CF14.2.15, CF14.2.16, CF15.2.15, CF15.2.16, CF16.2.15, CF16.2.16, CF17.2.15, CF17.2.16, CF18.2.15, CF18.2.16, CF20.2.15, CF20.2.16; also elsewhere on the board
OPD_SCL: CF13.2.13, CF13.2.14, CF14.2.13, CF14.2.14, CF15.2.13, CF15.2.14, CF16.2.13, CF16.2.14, CF17.2.13, CF17.2.14, CF18.2.13, CF18.2.14, CF20.2.13, CF20.2.14; also elsewhere on the board
OPD_SDA: CF13.2.11, CF13.2.12, CF14.2.11, CF14.2.12, CF15.2.11, CF15.2.12, CF16.2.11, CF16.2.12, CF17.2.11, CF17.2.12, CF18.2.11, CF18.2.12, CF20.2.11, CF20.2.12; also elsewhere on the board
SPARE07: CF13.2.7, CF14.2.7, CF15.2.7, CF16.2.7, CF17.2.7, CF18.2.7, CF20.2.7; also elsewhere on the board
SPARE08: CF13.2.8, CF14.2.8, CF15.2.8, CF16.2.8, CF17.2.8, CF18.2.8, CF20.2.8; also elsewhere on the board
SPARE09: CF13.2.9, CF14.2.9, CF15.2.9, CF16.2.9, CF17.2.9, CF18.2.9, CF20.2.9; also elsewhere on the board
SPARE10: CF13.2.10, CF14.2.10, CF15.2.10, CF16.2.10, CF17.2.10, CF18.2.10, CF20.2.10; also elsewhere on the board
SPARE21: CF13.2.21, CF14.2.21, CF15.2.21, CF16.2.21, CF17.2.21, CF18.2.21, CF20.2.21; also elsewhere on the board
SPARE22: CF13.2.22, CF14.2.22, CF15.2.22, CF16.2.22, CF17.2.22, CF18.2.22, CF20.2.22; also elsewhere on the board
SPARE31: CF13.2.31, CF14.2.31, CF15.2.31, CF16.2.31, CF17.2.31, CF18.2.31, CF20.2.31; also elsewhere on the board
SPARE32: CF13.2.32, CF14.2.32, CF15.2.32, CF16.2.32, CF17.2.32, CF18.2.32, CF20.2.32; also elsewhere on the board
VBUS: C13.1, C14.1, C15.1, C16.1, C17.1, C18.1, C20.1, CF13.2.23, CF13.2.24, CF13.2.25, CF13.2.26, CF14.2.23, CF14.2.24, CF14.2.25, CF14.2.26, CF15.2.23, CF15.2.24, CF15.2.25, CF15.2.26, CF16.2.23, CF16.2.24, CF16.2.25, CF16.2.26, CF17.2.23, CF17.2.24, CF17.2.25, CF17.2.26, CF18.2.23, CF18.2.24, CF18.2.25, CF18.2.26, CF20.2.23, CF20.2.24, CF20.2.25, CF20.2.26; also elsewhere on the board
~SD: CF13.2.39, CF13.2.40, CF14.2.39, CF14.2.40, CF15.2.39, CF15.2.40, CF16.2.39, CF16.2.40, CF17.2.39, CF17.2.40, CF18.2.39, CF18.2.40, CF20.2.39, CF20.2.40; also elsewhere on the board

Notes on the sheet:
Use R20.5,R20.6 to bridge CAN1 and CAN2
All resistors 0603 1% AEC-Q200 unless otherwise noted. All capacitors 0603 Vw >= 25V X7R AEC-Q200 unless otherwise noted.
